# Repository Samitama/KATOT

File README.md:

# KATOT Autonomous Car Team

Schematic Design

PCB Design

3D View

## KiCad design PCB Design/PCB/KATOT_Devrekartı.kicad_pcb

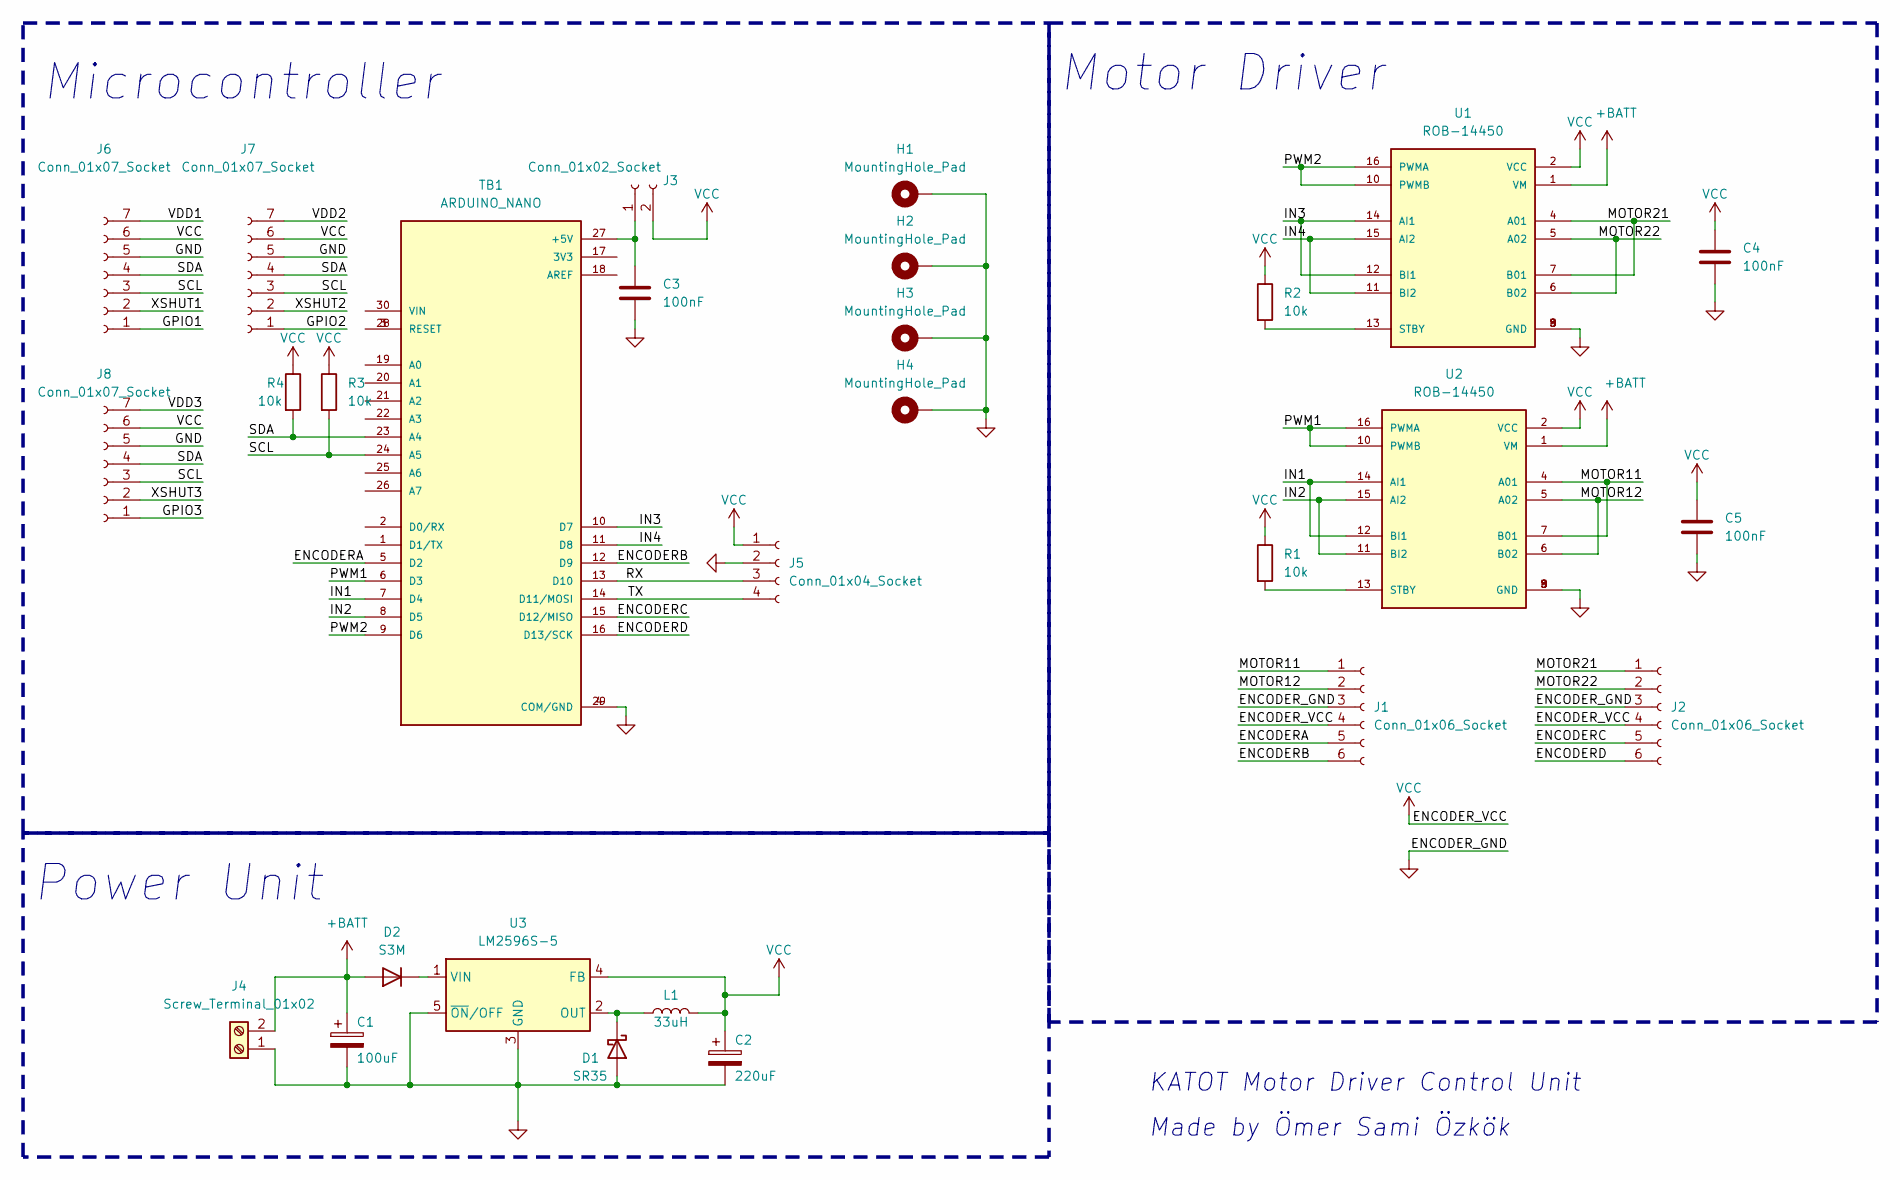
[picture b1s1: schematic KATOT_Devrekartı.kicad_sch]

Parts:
C1: 100uF; CP_Elec_6.3x7.7
C2: 220uF; CP_Elec_6.3x7.7
C3, C4, C5: 100nF; C_0805_2012Metric
D1: SR35; D_SMB-SMC_Universal_Handsoldering
D2: S3M; D_SMB-SMC_Universal_Handsoldering
H1, H2, H3, H4: MountingHole_Pad; MountingHole_3.2mm_M3_Pad_Via
J1, J2: Conn_01x06_Socket; PinHeader_1x06_P2.54mm_Vertical
J3: Conn_01x02_Socket; PinHeader_1x02_P2.54mm_Vertical
J4: Screw_Terminal_01x02; TerminalBlock_bornier-2_P5.08mm
J5: Conn_01x04_Socket; PinHeader_1x04_P2.54mm_Vertical
J6, J7, J8: Conn_01x07_Socket; PinSocket_1x07_P2.54mm_Vertical
L1: 33uH; L_12x12mm_H8mm
R1, R2, R3, R4: 10k; R_1206_3216Metric_Pad1.30x1.75mm_HandSolder
TB1: ARDUINO_NANO; SHIELD_ARDUINO_NANO
U1, U2: ROB-14450; MODULE_ROB-14450; PARTREV 11-13-17
U3: LM2596S-5; TO-263-5_TabPin3

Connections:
+BATT: C1.1, D2.2 (A), J4.2, U1.1 (VM), U2.1 (VM)
/ENCODERA: J1.5, TB1.5 (D2)
/ENCODERB: J1.6, TB1.12 (D9)
/ENCODERC: J2.5, TB1.15 (D12/MISO)
/ENCODERD: J2.6, TB1.16 (D13/SCK)
/GPIO1: J6.1
/GPIO2: J7.1
/GPIO3: J8.1
/IN1: TB1.7 (D4), U2.12 (BI1), U2.14 (AI1)
/IN2: TB1.8 (D5), U2.11 (BI2), U2.15 (AI2)
/IN3: TB1.10 (D7), U1.12 (BI1), U1.14 (AI1)
/IN4: TB1.11 (D8), U1.11 (BI2), U1.15 (AI2)
/MOTOR11: J1.1, U2.4 (A01), U2.7 (B01)
/MOTOR12: J1.2, U2.5 (A02), U2.6 (B02)
/MOTOR21: J2.1, U1.4 (A01), U1.7 (B01)
/MOTOR22: J2.2, U1.5 (A02), U1.6 (B02)
/PWM1: TB1.6 (D3), U2.10 (PWMB), U2.16 (PWMA)
/PWM2: TB1.9 (D6), U1.10 (PWMB), U1.16 (PWMA)
/RX: J5.3, TB1.13 (D10)
/SCL: J6.3, J7.3, J8.3, R3.2, TB1.24 (A5)
/SDA: J6.4, J7.4, J8.4, R4.2, TB1.23 (A4)
/TX: J5.4, TB1.14 (D11/MOSI)
/VDD1: J6.7
/VDD2: J7.7
/VDD3: J8.7
/XSHUT1: J6.2
/XSHUT2: J7.2
/XSHUT3: J8.2
GND: C1.2, C2.2, C3.2, C4.2, C5.2, D1.2 (A), H1.1, H2.1, H3.1, H4.1, J1.3, J2.3, J4.1, J5.2, J6.5, J7.5, J8.5, TB1.4 (COM/GND), TB1.29 (COM/GND), U1.3 (GND), U1.8 (GND), U1.9 (GND), U2.3 (GND), U2.8 (GND), U2.9 (GND), U3.3 (GND), U3.5 (~ON/OFF)
unnamed: D1.1 (K), L1.1, U3.2 (OUT)
unnamed: D2.1 (K), U3.1 (VIN)
unnamed: C3.1, J3.1, TB1.27 (+5V)
unnamed: TB1.3 (RESET), TB1.28 (RESET)
unnamed: R2.2, U1.13 (STBY)
unnamed: R1.2, U2.13 (STBY)
VCC: C2.1, C4.1, C5.1, J1.4, J2.4, J3.2, J5.1, J6.6, J7.6, J8.6, L1.2, R1.1, R2.1, R3.1, R4.1, U1.2 (VCC), U2.2 (VCC), U3.4 (FB)

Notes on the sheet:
Motor Driver
Microcontroller
Made by Ömer Sami Özkök
KATOT Motor Driver Control Unit
Power Unit

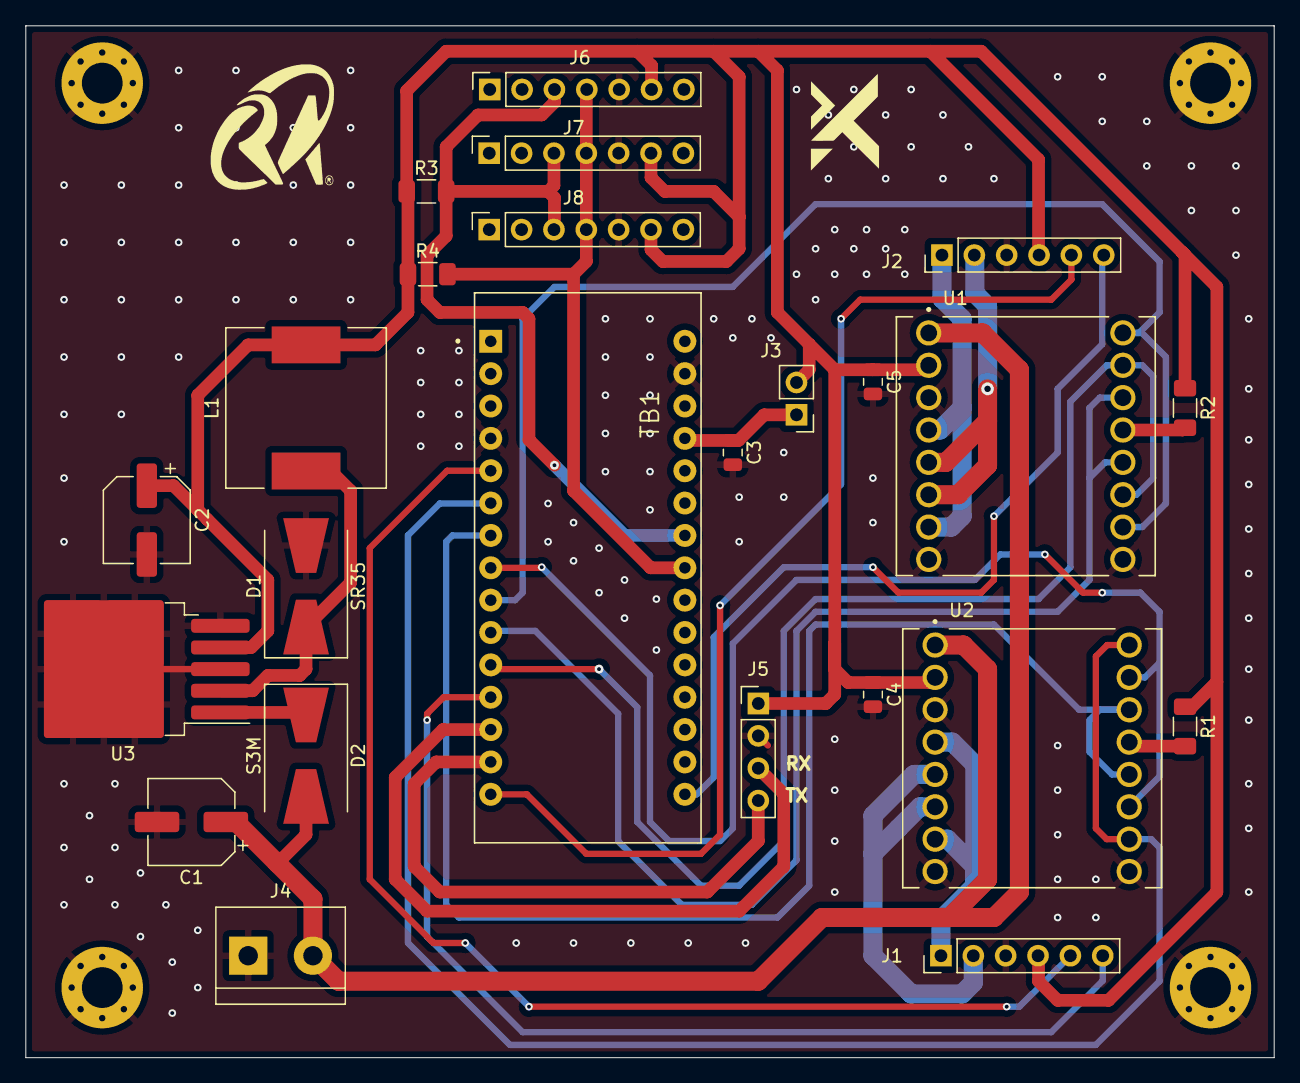
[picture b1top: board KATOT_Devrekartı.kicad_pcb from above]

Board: 2 copper layers, 98.0 x 81.0 mm, 28 parts (0 on the bottom side), 27 nets.

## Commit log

2023-09-17 main
2024-02-23 mian
2024-02-23 Examples_of_UART
2024-05-21 main
    update
2024-10-28 update
    update
2024-10-28 Update PCB_Demo.png
    PCB
